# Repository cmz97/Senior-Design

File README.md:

# Senior-Design
For Detail, please refer to my personal website [here](http://chengmingzhang.com/tech-projects/projects/blog-SeniorDesign.html)

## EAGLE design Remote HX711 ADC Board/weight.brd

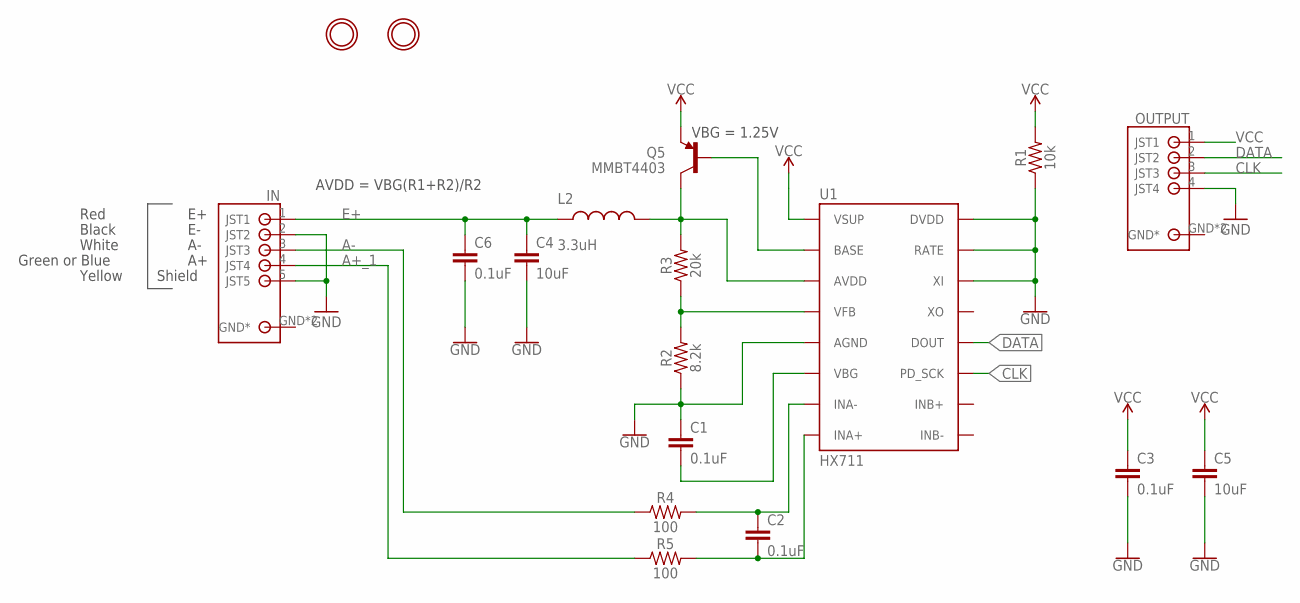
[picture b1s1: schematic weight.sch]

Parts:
C1, C2, C3, C6: 0.1uF; 0603
C4, C5: 10uF; 0603
IN: S5B-PH-SM4_TB
L2: 3.3uH; 0805
OUTPUT: S4B-PH-SM4_TB
Q5: MMBT4403; SOT23-3
R1: 10k; 0603
R2: 8.2k; 0603
R3: 20k; 0603
R4, R5: 100; 0603
U1: HX711; SO16
U$4, U$49: MOUNTINGHOLE2.5; MOUNTINGHOLE_2.5_PLATED

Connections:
A+_1: IN.4 (JST4), R5.1
A-: IN.3 (JST3), R4.1
CLK: OUTPUT.3 (JST3), U1.11 (PD_SCK)
DATA: OUTPUT.2 (JST2), U1.12 (DOUT)
E+: C4.1, C6.1, IN.1 (JST1), L2.1
GND: C1.1, C3.2, C4.2, C5.2, C6.2, IN.2 (JST2), IN.5 (JST5), OUTPUT.4 (JST4), R1.1, R2.1, U1.5 (AGND), U1.14 (XI), U1.15 (RATE), U1.16 (DVDD)
unnamed: C2.2, R5.2, U1.8 (INA+)
unnamed: Q5.1 (B), U1.2 (BASE)
unnamed: R2.2, R3.1, U1.4 (VFB)
unnamed: C1.2, U1.6 (VBG)
unnamed: L2.2, Q5.3 (C), R3.2, U1.3 (AVDD)
unnamed: C2.1, R4.2, U1.7 (INA-)
VCC: C3.1, C5.1, OUTPUT.1 (JST1), Q5.2 (E), R1.2, U1.1 (VSUP)

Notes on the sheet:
AVDD = VBG(R1+R2)/R2
Red
Black
White
Green or Blue
Shield
Yellow
VBG = 1.25V

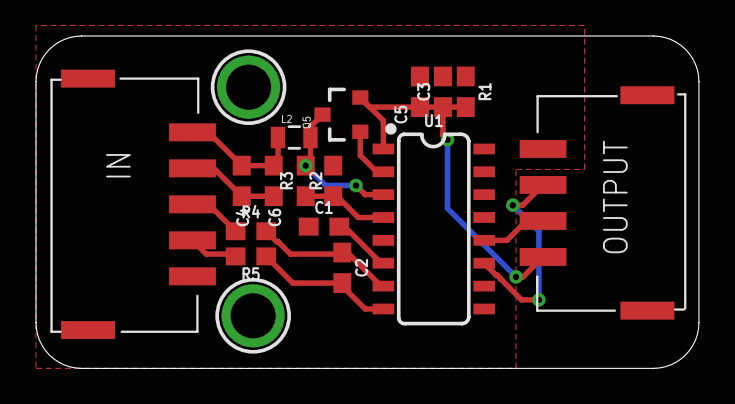
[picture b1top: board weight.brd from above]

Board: 2 copper layers, 36.8 x 18.5 mm, 18 parts (0 on the bottom side), 13 nets.

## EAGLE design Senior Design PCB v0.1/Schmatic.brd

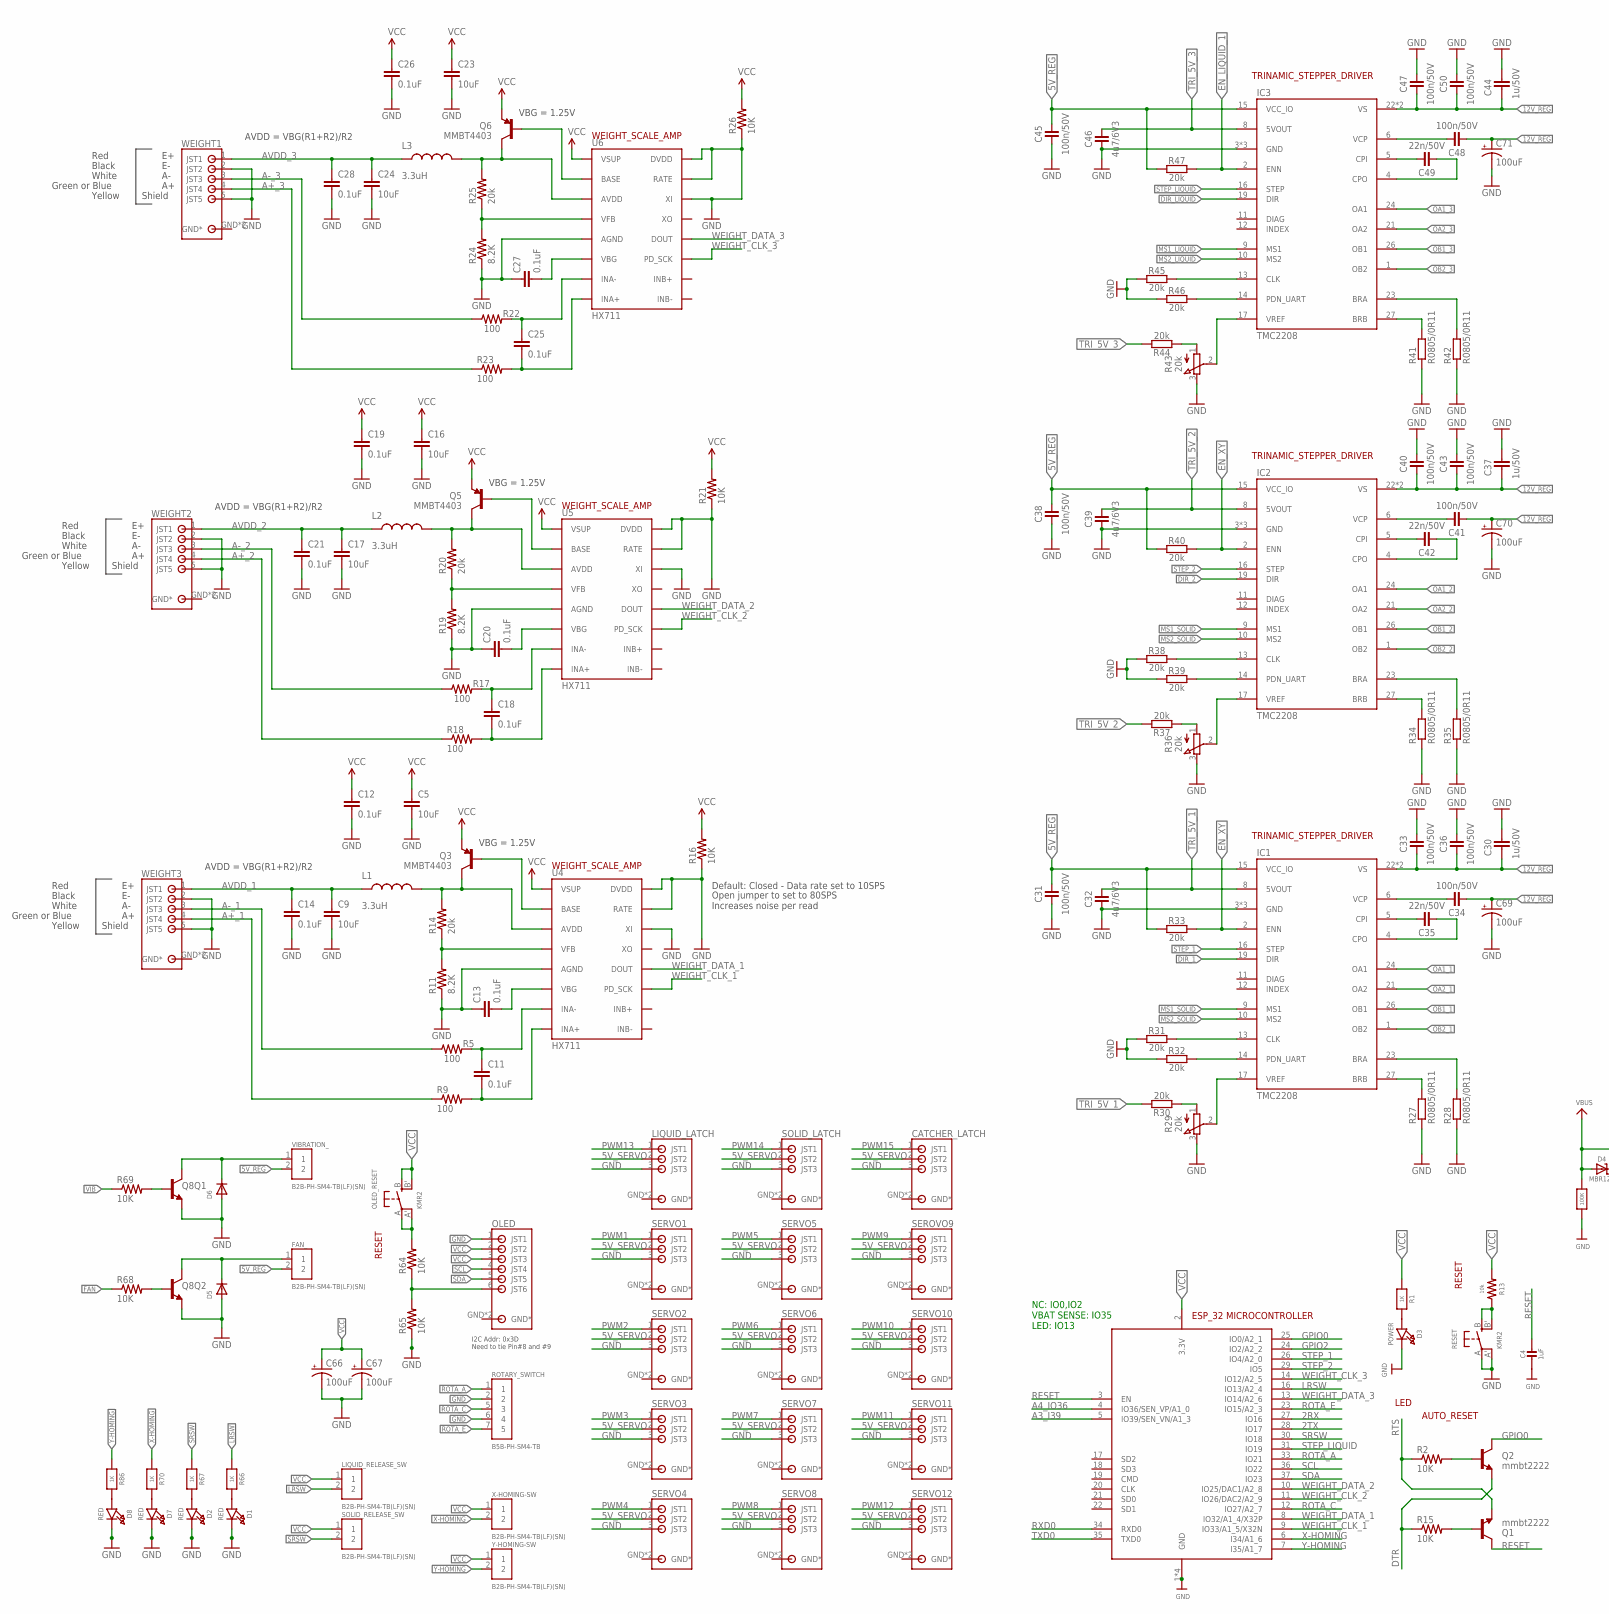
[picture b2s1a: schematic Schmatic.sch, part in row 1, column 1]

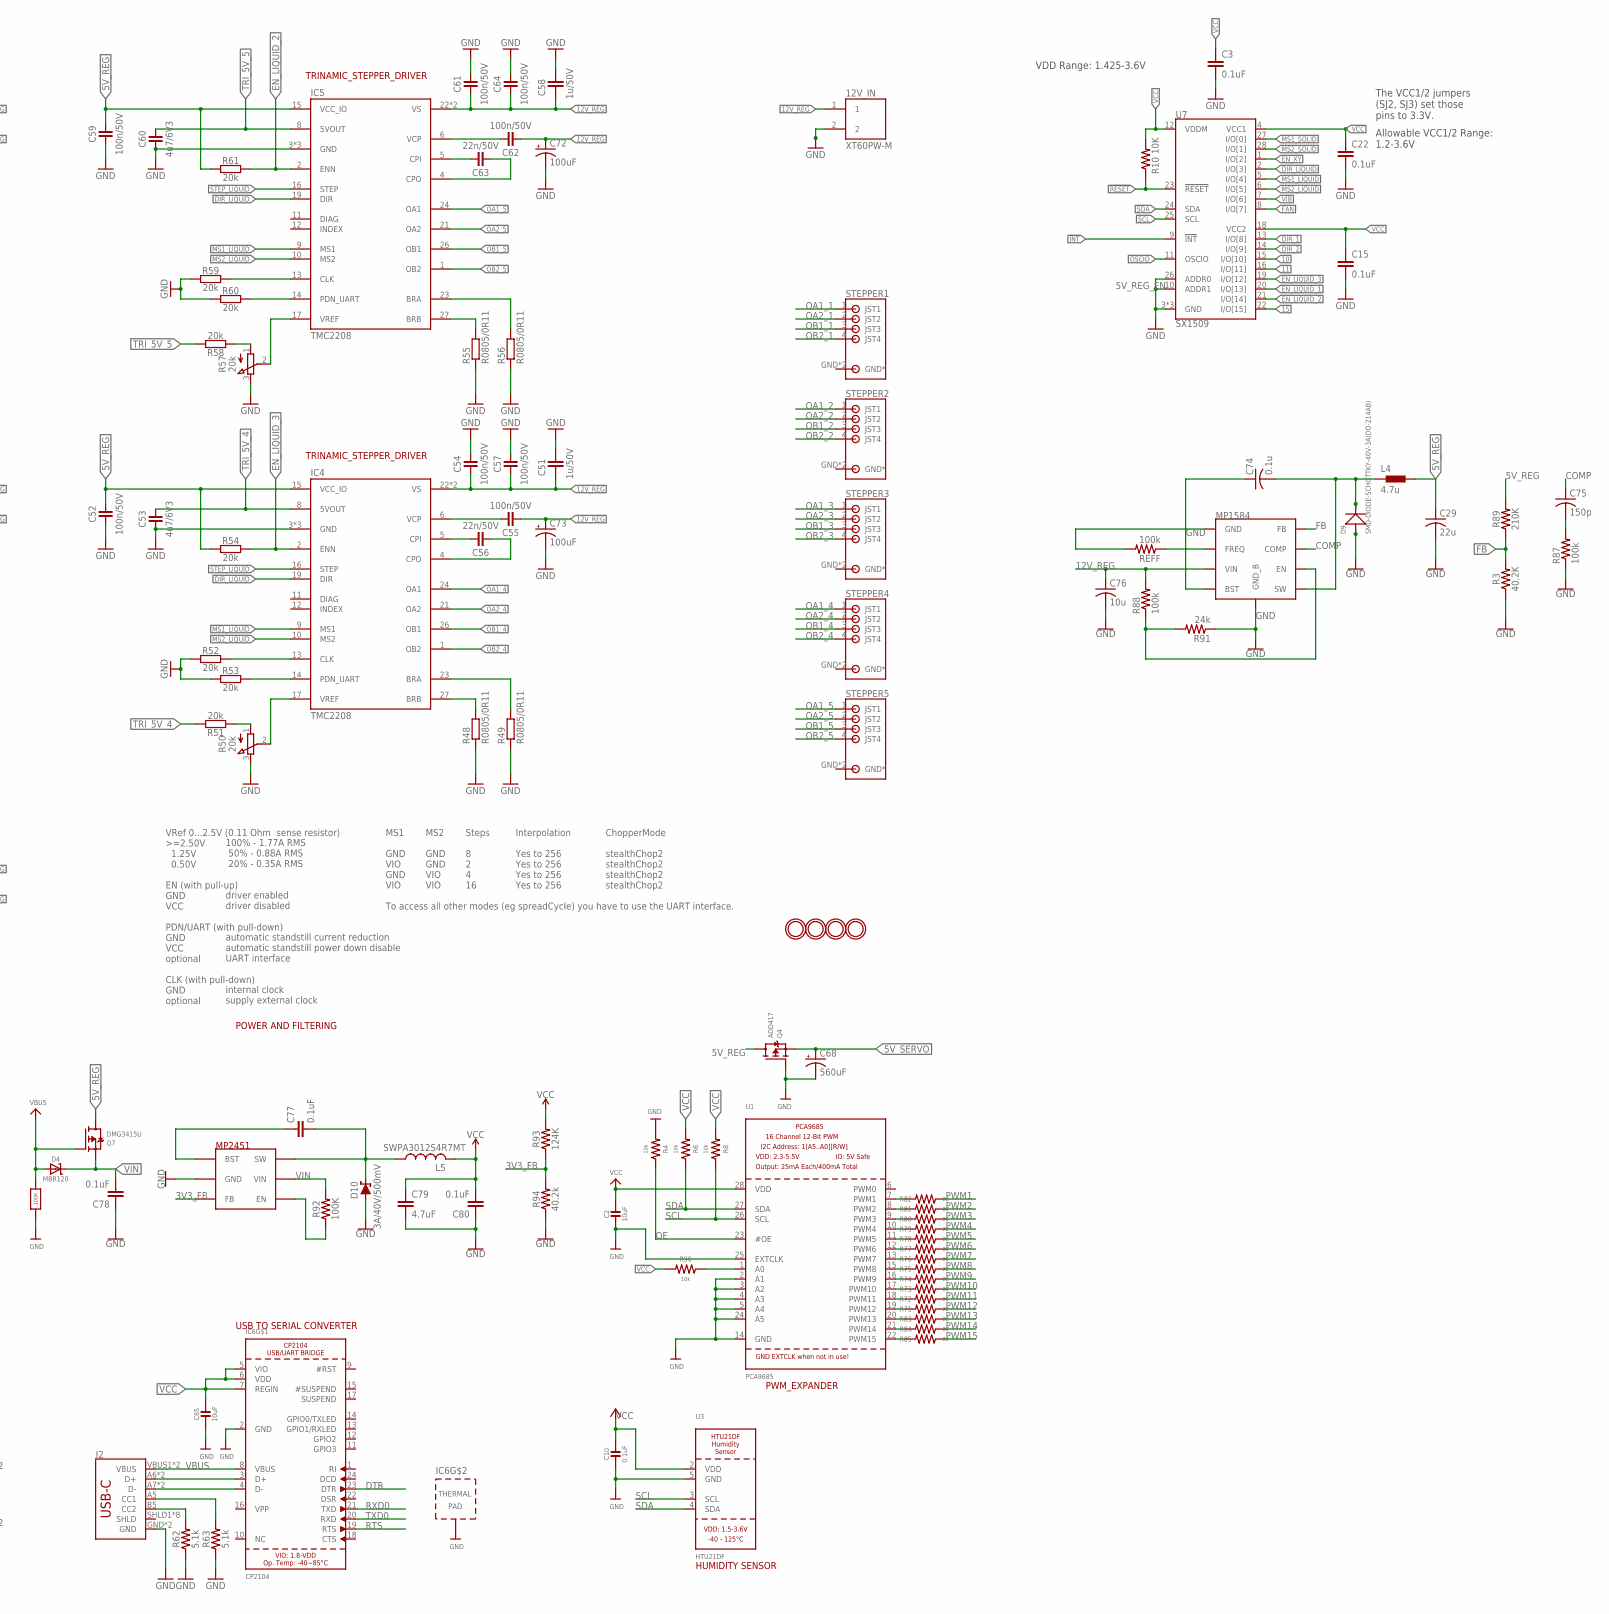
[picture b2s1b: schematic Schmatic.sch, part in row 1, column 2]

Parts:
12V_IN: XT60PW-M; AMASS_XT60PW-M
C2, C65: 10uF; 0805-NO
C3, C15, C22: 0.1uF; 0603-CAP
C4: 1uF; 0603-NO
C5, C9, C16, C17, C23, C24: 10uF; 1210
C10: 0.1uF; 0805-NO
C11, C12, C13, C14, C18, C19, C20, C21, C25, C26, C27, C28: 0.1uF; 0603-CAP@1
C29: 22u; C1206
C30, C37, C44, C51, C58: 1u/50V; C0805
C31, C33, C34, C36, C38, C40, C41, C43, C45, C47, C48, C50, C52, C54, C55, C57, C59, C61, C62, C64: 100n/50V; C0402
C32, C39, C46, C53, C60: 4u7/6V3; C0402
C35, C42, C49, C56, C63: 22n/50V; C0402
C66, C67, C69, C70, C71, C72, C73: 100uF; PANASONIC_D
C68: 560uF; PANASONIC_G
C74: 0.1u; C0603
C75: 150p; C0603
C76: 10u; C1206
C77, C78, C80: 0.1uF; 0603
C79: 4.7uF; 1206
CATCHER_LATCH: S3B-PH-SM4_TB
D1, D2, D7, D8: RED; CHIPLED_0805_NOOUTLINE
D3: POWER; CHIPLED_0805_NOOUTLINE
D4: MBR120; SOD-123
D5, D6: DIODESOD-323F; SOD-323F
D9: SMD-DIODE-SCHOTTKY-40V-3A(DO-214AB); DO-214AB
D10: 3A/40V/500mV; SMA-DIODE
FAN_: B2B-PH-SM4-TB(LF)(SN); JST_B2B-PH-SM4-TB(LF)(SN)
IC1, IC2, IC3, IC4, IC5: TMC2208; QFN28-PAD
IC6: CP2104; QFN24_4MM_SMSC
J2: USB_C16PIN; USB-C-16P
L1, L2, L3: 3.3uH; 0805
L4: 4.7u; MHCI0603-4R7M-R8
L5: SWPA3012S4R7MT; L3230M
LIQUID_LATCH: S3B-PH-SM4_TB
LIQUID_RELEASE_SW: B2B-PH-SM4-TB(LF)(SN); JST_B2B-PH-SM4-TB(LF)(SN)
MP2451: MP2451; TSOT-23-6-SOT-23-6
OLED: S6B-PH-SM4_TB
OLED_RESET: KMR2; BTN_KMR2_4.6X2.8
Q1, Q2: mmbt2222; SOT23-3
Q3, Q5, Q6: MMBT4403; SOT23-3
Q4: AOD417; TO252
Q7: DMG3415U; SOT23-R
Q8: TRANS_NPN_DUAL-MBT3904DW1T1; SC70-6
R1, R66, R67, R70, R86: 1K; 0603-NO
R2, R10, R15, R16, R21, R26, R64, R65, R68, R69: 10K; 0603-RES
R3: 40.2K; 0603
R4, R6, R8, R13, R90: 10k; 0603
R5, R9, R17, R18, R22, R23: 100; 0603-RES@1
R11, R19, R24: 8.2K; 0603-RES@1
R12: 100K; 0603-NO
R14, R20, R25: 20k; 0603-RES@1
R27, R28, R34, R35, R41, R42, R48, R49, R55, R56: R0805/0R11; M0805
R29, R36, R43, R50, R57: 20k; POT_EVM3R
R30, R31, R32, R33, R37, R38, R39, R40, R44, R45, R46, R47, R51, R52, R53, R54, R58, R59, R60, R61: 20k; C0402
R62, R63: 5.1k; 0603
R71, R72, R73, R74, R75, R76, R77, R78, R79, R80, R81, R82, R83, R84, R85: 22; 0603
R87, R88: 100k; R0603
R89: 210K; 0603
R91: 24k; R0603
R92: 100K; 0603
R93: 124K; 0603
R94: 40.2k; 0603
REFF: 100k; R0603
RESET: KMR2; BTN_KMR2_4.6X2.8
ROTARY_SWITCH: B5B-PH-SM4-TB; JST_B5B-PH-SM4-TB
SEROVO9: S3B-PH-SM4_TB
SERVO1, SERVO2, SERVO3, SERVO4, SERVO5, SERVO6, SERVO7, SERVO8, SERVO10, SERVO11, SERVO12: S3B-PH-SM4_TB
SOLID_LATCH: S3B-PH-SM4_TB
SOLID_RELEASE_SW: B2B-PH-SM4-TB(LF)(SN); JST_B2B-PH-SM4-TB(LF)(SN)
STEPPER1, STEPPER2, STEPPER3, STEPPER4, STEPPER5: S4B-PH-SM4_TB
U1: PCA9685; TSSOP28
U3: HTU21DF
U4, U5, U6: HX711; SO16
U7: SX1509; QFN-28
U$2: MP1584_V2
U$4, U$48, U$49, U$50: MOUNTINGHOLE2.5; MOUNTINGHOLE_2.5_PLATED
VIBRATION_: B2B-PH-SM4-TB(LF)(SN); JST_B2B-PH-SM4-TB(LF)(SN)
WEIGHT1, WEIGHT2, WEIGHT3: S5B-PH-SM4_TB
X2: ESP32_WROOM32_SKINNY; WROOM32_SKINNY
X-HOMING-SW: B2B-PH-SM4-TB(LF)(SN); JST_B2B-PH-SM4-TB(LF)(SN)
Y-HOMING-SW: B2B-PH-SM4-TB(LF)(SN); JST_B2B-PH-SM4-TB(LF)(SN)

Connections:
2RX: X2.27 (IO16)
2TX: X2.28 (IO17)
3V3_FB: MP2451.PIN3 (FB), R93.1, R94.2
5V_REG: C29.1, C31.2, C38.2, C45.2, C52.2, C59.2, FAN_.2, IC1.15 (VCC_IO), IC2.15 (VCC_IO), IC3.15 (VCC_IO), IC4.15 (VCC_IO), IC5.15 (VCC_IO), L4.P$2 (2), Q4.3 (D), Q7.3 (D), R33.1, R40.1, R47.1, R54.1, R61.1, R89.2, VIBRATION_.2
5V_REG_EN: R88.1, R91.2, U$2.EN
5V_SERVO: C68.+, CATCHER_LATCH.2 (JST2), LIQUID_LATCH.2 (JST2), Q4.2 (S), SEROVO9.2 (JST2), SERVO1.2 (JST2), SERVO2.2 (JST2), SERVO3.2 (JST2), SERVO4.2 (JST2), SERVO5.2 (JST2), SERVO6.2 (JST2), SERVO7.2 (JST2), SERVO8.2 (JST2), SERVO10.2 (JST2), SERVO11.2 (JST2), SERVO12.2 (JST2), SOLID_LATCH.2 (JST2)
10: U7.15 (I/O[10])
11: U7.16 (I/O[11])
12V_REG: 12V_IN.1, C30.1, C33.1, C34.1, C36.1, C37.1, C40.1, C41.1, C43.1, C44.1, C47.1, C48.1, C50.1, C51.1, C54.1, C55.1, C57.1, C58.1, C61.1, C62.1, C64.1, C69.+, C70.+, C71.+, C72.+, C73.+, C76.1, IC1.22 (VS), IC1.28 (VS), IC2.22 (VS), IC2.28 (VS), IC3.22 (VS), IC3.28 (VS), IC4.22 (VS), IC4.28 (VS), IC5.22 (VS), IC5.28 (VS), R88.2, U$2.VIN
15: U7.22 (I/O[15])
!INT: U7.9 (!INT)
!RESET: R10.1, U7.23 (!RESET)
A3_I39: X2.5 (IO39/SEN_VN/A1_3)
A4_IO36: X2.4 (IO36/SEN_VP/A1_0)
A+_1: R9.1, WEIGHT3.4 (JST4)
A+_2: R18.1, WEIGHT2.4 (JST4)
A+_3: R23.1, WEIGHT1.4 (JST4)
A-_1: R5.1, WEIGHT3.3 (JST3)
A-_2: R17.1, WEIGHT2.3 (JST3)
A-_3: R22.1, WEIGHT1.3 (JST3)
AVDD_1: C9.1, C14.1, L1.1, WEIGHT3.1 (JST1)
AVDD_2: C17.1, C21.1, L2.1, WEIGHT2.1 (JST1)
AVDD_3: C24.1, C28.1, L3.1, WEIGHT1.1 (JST1)
BRA: IC1.23 (BRA), R28.2
BRA1: IC2.23 (BRA), R35.2
BRA2: IC3.23 (BRA), R42.2
BRA3: IC4.23 (BRA), R49.2
BRA4: IC5.23 (BRA), R56.2
BRB: IC1.27 (BRB), R27.2
BRB1: IC2.27 (BRB), R34.2
BRB2: IC3.27 (BRB), R41.2
BRB3: IC4.27 (BRB), R48.2
BRB4: IC5.27 (BRB), R55.2
BST: C74.1, U$2.BST
CC1: J2.A5 (CC1), R63.2
CC2: J2.B5 (CC2), R62.2
CLK_1: IC1.13 (CLK), R31.2
CLK_2: IC2.13 (CLK), R38.2
CLK_3: IC3.13 (CLK), R45.2
CLK_4: IC4.13 (CLK), R52.2
CLK_5: IC5.13 (CLK), R59.2
COMP: C75.1, U$2.COMP
CPI: C35.2, IC1.5 (CPI)
CPI1: C42.2, IC2.5 (CPI)
CPI2: C49.2, IC3.5 (CPI)
CPI3: C56.2, IC4.5 (CPI)
CPI4: C63.2, IC5.5 (CPI)
CPO: C35.1, IC1.4 (CPO)
CPO1: C42.1, IC2.4 (CPO)
CPO2: C49.1, IC3.4 (CPO)
CPO3: C56.1, IC4.4 (CPO)
CPO4: C63.1, IC5.4 (CPO)
DIR_1: IC1.19 (DIR), U7.13 (I/O[8])
DIR_2: IC2.19 (DIR), U7.14 (I/O[9])
DIR_LIQUID: IC3.19 (DIR), IC4.19 (DIR), IC5.19 (DIR), U7.2 (I/O[3])
DTR: IC6.23 (DTR), Q2.2 (E), R15.1
EN_LIQUID_1: IC3.2 (ENN), R47.2, U7.20 (I/O[13])
EN_LIQUID_2: IC5.2 (ENN), R61.2, U7.21 (I/O[14])
EN_LIQUID_3: IC4.2 (ENN), R54.2, U7.19 (I/O[12])
EN_XY: IC1.2 (ENN), IC2.2 (ENN), R33.2, R40.2, U7.1 (I/O[2])
FAN: R68.1, U7.8 (I/O[7])
FAN_5V: D5.C, FAN_.1, Q8.6 (C)
FB: R3.2, R89.1, U$2.FB
FREQ: REFF.1, U$2.FREQ
GND: 12V_IN.2, C2.2, C3.2, C4.2, C5.2, C9.2, C10.2, C12.2, C13.1, C14.2, C15.2, C16.2, C17.2, C19.2, C20.1, C21.2, C22.2, C23.2, C24.2, C26.2, C27.1, C28.2, C29.2, C30.2, C31.1, C32.1, C33.2, C36.2, C37.2, C38.1, C39.1, C40.2, C43.2, C44.2, C45.1, C46.1, C47.2, C50.2, C51.2, C52.1, C53.1, C54.2, C57.2, C58.2, C59.1, C60.1, C61.2, C64.2, C65.2, C66.-, C67.-, C68.-, C69.-, C70.-, C71.-, C72.-, C73.-, C76.2, C78.1, C79.2, C80.1, CATCHER_LATCH.3 (JST3), D1.C, D2.C, D3.C, D5.A, D6.A, D7.C, D8.C, D9.1 (+), D10.A, IC1.3 (GND), IC1.18 (GND), IC1.TP (GND), IC2.3 (GND), IC2.18 (GND), IC2.TP (GND), IC3.3 (GND), IC3.18 (GND), IC3.TP (GND), IC4.3 (GND), IC4.18 (GND), IC4.TP (GND), IC5.3 (GND), IC5.18 (GND), IC5.TP (GND), IC6.2 (GND), IC6.THERM (TP), J2.GND, J2.GND2 (GND), LIQUID_LATCH.3 (JST3), MP2451.PIN2 (GND), OLED.1 (JST1), Q4.1 (G), Q8.1 (E), Q8.4 (E), R3.1, R4.2, R11.1, R12.1, R16.1, R19.1, R21.1, R24.1, R26.1, R27.1, R28.1, R29.3 (E), R31.1, R32.1, R34.1, R35.1, R36.3 (E), R38.1, R39.1, R41.1, R42.1, R43.3 (E), R45.1, R46.1, R48.1, R49.1, R50.3 (E), R52.1, R53.1, R55.1, R56.1, R57.3 (E), R59.1, R60.1, R62.1, R63.1, R65.1, R87.1, R91.1, R94.1, REFF.2, RESET.A, RESET.A' (P1), ROTARY_SWITCH.2, ROTARY_SWITCH.6 (4), SEROVO9.3 (JST3), SERVO1.3 (JST3), SERVO2.3 (JST3), SERVO3.3 (JST3), SERVO4.3 (JST3), SERVO5.3 (JST3), SERVO6.3 (JST3), SERVO7.3 (JST3), SERVO8.3 (JST3), SERVO10.3 (JST3), SERVO11.3 (JST3), SERVO12.3 (JST3), SOLID_LATCH.3 (JST3), U1.2 (A1), U1.3 (A2), U1.4 (A3), U1.5 (A4), U1.14 (GND), U1.24 (A5), U1.25 (EXTCLK), U3.5 (GND), U4.5 (AGND), U4.14 (XI), U4.15 (RATE), U4.16 (DVDD), U5.5 (AGND), U5.14 (XI), U5.15 (RATE), U5.16 (DVDD), U6.5 (AGND), U6.14 (XI), U6.15 (RATE), U6.16 (DVDD), U7.3 (GND), U7.10 (ADDR1), U7.17 (GND), U7.26 (ADDR0), U7.29 (GND), U$2.GND, U$2.GND_B, WEIGHT1.2 (JST2), WEIGHT1.5 (JST5), WEIGHT2.2 (JST2), WEIGHT2.5 (JST5), WEIGHT3.2 (JST2), WEIGHT3.5 (JST5), X2.1 (GND), X2.15 (GND), X2.38 (GND), X2.P$1 (GND)
GPIO0: Q2.3 (C), X2.25 (IO0/A2_1)
GPIO2: X2.24 (IO2/A2_2)
LRSW: LIQUID_RELEASE_SW.2, R66.1, X2.16 (IO13/A2_4)
MS1_LIQUID: IC3.9 (MS1), IC4.9 (MS1), IC5.9 (MS1), U7.5 (I/O[4])
MS1_SOLID: IC1.9 (MS1), IC2.9 (MS1), U7.27 (I/O[0])
MS2_LIQUID: IC3.10 (MS2), IC4.10 (MS2), IC5.10 (MS2), U7.6 (I/O[5])
MS2_SOLID: IC1.10 (MS2), IC2.10 (MS2), U7.28 (I/O[1])
unnamed: C13.2, U4.6 (VBG)
unnamed: L1.2, Q3.3 (C), R14.2, U4.3 (AVDD)
unnamed: Q5.1 (B), U5.2 (BASE)
unnamed: Q3.1 (B), U4.2 (BASE)
unnamed: D3.A, R1.2
unnamed: R11.2, R14.1, U4.4 (VFB)
unnamed: C11.1, R5.2, U4.7 (INA-)
unnamed: C11.2, R9.2, U4.8 (INA+)
unnamed: C75.2, R87.2
unnamed: R19.2, R20.1, U5.4 (VFB)
unnamed: Q1.1 (B), R15.2
unnamed: Q2.1 (B), R2.2
unnamed: C20.2, U5.6 (VBG)
unnamed: L2.2, Q5.3 (C), R20.2, U5.3 (AVDD)
unnamed: C18.1, R17.2, U5.7 (INA-)
unnamed: C18.2, R18.2, U5.8 (INA+)
unnamed: OLED_RESET.A, OLED_RESET.A' (P1), R64.2
unnamed: Q6.1 (B), U6.2 (BASE)
unnamed: R24.2, R25.1, U6.4 (VFB)
unnamed: C27.2, U6.6 (VBG)
unnamed: L3.2, Q6.3 (C), R25.2, U6.3 (AVDD)
unnamed: C25.1, R22.2, U6.7 (INA-)
unnamed: C25.2, R23.2, U6.8 (INA+)
unnamed: MP2451.PIN4 (EN), R92.1
unnamed: IC6.3 (D+), J2.A6 (D+), J2.B6 (D+)
unnamed: IC6.4 (D-), J2.A7 (D-), J2.B7 (D-)
unnamed: C77.1, MP2451.PIN1 (BST)
unnamed: R90.1, U1.1 (A0)
unnamed: C77.2, D10.C, L5.1, MP2451.PIN6 (SW)
unnamed: D1.A, R66.2
unnamed: OLED.6 (JST6), R64.1, R65.2
unnamed: Q8.5 (B), R69.2
unnamed: D2.A, R67.2
unnamed: Q8.2 (B), R68.2
unnamed: R71.2, U1.19 (PWM12)
unnamed: R72.2, U1.18 (PWM11)
unnamed: R73.2, U1.17 (PWM10)
unnamed: R74.2, U1.16 (PWM9)
unnamed: R75.2, U1.15 (PWM8)
unnamed: R76.2, U1.13 (PWM7)
unnamed: R77.2, U1.12 (PWM6)
unnamed: R78.2, U1.11 (PWM5)
unnamed: R79.2, U1.10 (PWM4)
unnamed: R80.2, U1.9 (PWM3)
unnamed: R81.2, U1.8 (PWM2)
unnamed: R82.2, U1.7 (PWM1)
unnamed: R83.2, U1.20 (PWM13)
unnamed: R84.2, U1.21 (PWM14)
unnamed: R85.2, U1.22 (PWM15)
unnamed: D7.A, R70.2
unnamed: R13.1, RESET.B (S), RESET.B' (S1)
unnamed: D8.A, R86.2
OA1_1: IC1.24 (OA1), STEPPER1.1 (JST1)
OA1_2: IC2.24 (OA1), STEPPER2.1 (JST1)
OA1_3: IC3.24 (OA1), STEPPER3.1 (JST1)
OA1_4: IC4.24 (OA1), STEPPER4.1 (JST1)
OA1_5: IC5.24 (OA1), STEPPER5.1 (JST1)
OA2_1: IC1.21 (OA2), STEPPER1.2 (JST2)
OA2_2: IC2.21 (OA2), STEPPER2.2 (JST2)
OA2_3: IC3.21 (OA2), STEPPER3.2 (JST2)
OA2_4: IC4.21 (OA2), STEPPER4.2 (JST2)
OA2_5: IC5.21 (OA2), STEPPER5.2 (JST2)
OB1_1: IC1.26 (OB1), STEPPER1.3 (JST3)
OB1_2: IC2.26 (OB1), STEPPER2.3 (JST3)
OB1_3: IC3.26 (OB1), STEPPER3.3 (JST3)
OB1_4: IC4.26 (OB1), STEPPER4.3 (JST3)
OB1_5: IC5.26 (OB1), STEPPER5.3 (JST3)
OB2_1: IC1.1 (OB2), STEPPER1.4 (JST4)
OB2_2: IC2.1 (OB2), STEPPER2.4 (JST4)
OB2_3: IC3.1 (OB2), STEPPER3.4 (JST4)
OB2_4: IC4.1 (OB2), STEPPER4.4 (JST4)
OB2_5: IC5.1 (OB2), STEPPER5.4 (JST4)
OE: R4.1, U1.23 (#OE)
OSCIO: U7.11 (OSCIO)
PDN_UART_1: IC1.14 (PDN_UART), R32.2
PDN_UART_2: IC2.14 (PDN_UART), R39.2
PDN_UART_3: IC3.14 (PDN_UART), R46.2
PDN_UART_4: IC4.14 (PDN_UART), R53.2
PDN_UART_5: IC5.14 (PDN_UART), R60.2
PWM1: R82.1, SERVO1.1 (JST1)
PWM2: R81.1, SERVO2.1 (JST1)
PWM3: R80.1, SERVO3.1 (JST1)
PWM4: R79.1, SERVO4.1 (JST1)
PWM5: R78.1, SERVO5.1 (JST1)
PWM6: R77.1, SERVO6.1 (JST1)
PWM7: R76.1, SERVO7.1 (JST1)
PWM8: R75.1, SERVO8.1 (JST1)
PWM9: R74.1, SEROVO9.1 (JST1)
PWM10: R73.1, SERVO10.1 (JST1)
PWM11: R72.1, SERVO11.1 (JST1)
PWM12: R71.1, SERVO12.1 (JST1)
PWM13: LIQUID_LATCH.1 (JST1), R83.1
PWM14: R84.1, SOLID_LATCH.1 (JST1)
PWM15: CATCHER_LATCH.1 (JST1), R85.1
RESET: C4.1, Q1.3 (C), X2.3 (EN)
ROTA_A: ROTARY_SWITCH.1, X2.33 (IO21)
ROTA_C: ROTARY_SWITCH.5 (3), X2.12 (IO27/A2_7)
ROTA_E: ROTARY_SWITCH.7 (5), X2.23 (IO15/A2_3)
RTS: IC6.19 (RTS), Q1.2 (E), R2.1
RXD0: IC6.21 (TXD), X2.34 (RXD0)
SCL: OLED.4 (JST4), R8.1, U1.26 (SCL), U3.3 (SCL), U7.25 (SCL), X2.36 (IO22)
SDA: OLED.5 (JST5), R6.1, U1.27 (SDA), U3.4 (SDA), U7.24 (SDA), X2.37 (IO23)
SRSW: R67.1, SOLID_RELEASE_SW.2, X2.30 (IO18)
STEP_1: IC1.16 (STEP), X2.26 (IO4/A2_0)
STEP_2: IC2.16 (STEP), X2.29 (IO5)
STEP_LIQUID: IC3.16 (STEP), IC4.16 (STEP), IC5.16 (STEP), X2.31 (IO19)
SW: C74.2, D9.2 (-), L4.P$1 (1), U$2.SW
TRI_5V_1: C32.2, IC1.8 (5VOUT), R30.2
TRI_5V_2: C39.2, IC2.8 (5VOUT), R37.2
TRI_5V_3: C46.2, IC3.8 (5VOUT), R44.2
TRI_5V_4: C53.2, IC4.8 (5VOUT), R51.2
TRI_5V_5: C60.2, IC5.8 (5VOUT), R58.2
TXD0: IC6.20 (RXD), X2.35 (TXD0)
VBUS: D4.A, IC6.8 (VBUS), J2.VBUS1 (VBUS), J2.VBUS2 (VBUS), Q7.1 (G), R12.2
VCC: C2.1, C3.1, C5.1, C10.1, C12.1, C15.1, C16.1, C19.1, C22.1, C23.1, C26.1, C65.1, C66.+, C67.+, C79.1, C80.2, IC6.5 (VIO), IC6.6 (VDD), IC6.7 (REGIN), L5.2, LIQUID_RELEASE_SW.1, OLED.2 (JST2), OLED.3 (JST3), OLED_RESET.B (S), OLED_RESET.B' (S1), Q3.2 (E), Q5.2 (E), Q6.2 (E), R1.1, R6.2, R8.2, R10.2, R13.2, R16.2, R21.2, R26.2, R90.2, R93.2, SOLID_RELEASE_SW.1, U1.28 (VDD), U3.2 (VDD), U4.1 (VSUP), U5.1 (VSUP), U6.1 (VSUP), U7.4 (VCC1), U7.12 (VDDM), U7.18 (VCC2), X2.2 (3.3V), X-HOMING-SW.1, Y-HOMING-SW.1
VCP: C34.2, IC1.6 (VCP)
VCP1: C41.2, IC2.6 (VCP)
VCP2: C48.2, IC3.6 (VCP)
VCP3: C55.2, IC4.6 (VCP)
VCP4: C62.2, IC5.6 (VCP)
VIB: R69.1, U7.7 (I/O[6])
VIB_5V: D6.C, Q8.3 (C), VIBRATION_.1
VIN: C78.2, D4.C, MP2451.PIN5 (VIN), Q7.2 (S), R92.2
VREF: IC1.17 (VREF), R29.2 (S)
VREF1: R29.1 (A), R30.1
VREF2: IC2.17 (VREF), R36.2 (S)
VREF3: R36.1 (A), R37.1
VREF4: IC3.17 (VREF), R43.2 (S)
VREF5: R43.1 (A), R44.1
VREF6: IC4.17 (VREF), R50.2 (S)
VREF7: R50.1 (A), R51.1
VREF8: IC5.17 (VREF), R57.2 (S)
VREF9: R57.1 (A), R58.1
WEIGHT_CLK_1: U4.11 (PD_SCK), X2.9 (IO33/A1_5/X32N)
WEIGHT_CLK_2: U5.11 (PD_SCK), X2.11 (IO26/DAC2/A2_9)
WEIGHT_CLK_3: U6.11 (PD_SCK), X2.14 (IO12/A2_5)
WEIGHT_DATA_1: U4.12 (DOUT), X2.8 (IO32/A1_4/X32P)
WEIGHT_DATA_2: U5.12 (DOUT), X2.10 (IO25/DAC1/A2_8)
WEIGHT_DATA_3: U6.12 (DOUT), X2.13 (IO14/A2_6)
X-HOMING: R70.1, X2.6 (I34/A1_6), X-HOMING-SW.2
Y-HOMING: R86.1, X2.7 (I35/A1_7), Y-HOMING-SW.2

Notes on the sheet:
NC: IO0,IO2 VBAT SENSE: IO35 LED: IO13
POWER AND FILTERING
RESET
VBG = 1.25V
AVDD = VBG(R1+R2)/R2
Default: Closed - Data rate set to 10SPS
Open jumper to set to 80SPS Increases noise per read
Red
Black
White
Green or Blue
Shield
Yellow
VRef 0...2.5V (0.11 Ohm sense resistor) >=2.50V 1.25V 0.50V EN (with pull-up) GND VCC PDN/UART (with pull-down) GND VCC optional CLK (with pull-down) GND optional
100% - 1.77A RMS 50% - 0.88A RMS 20% - 0.35A RMS driver enabled driver disabled automatic standstill current reduction automatic standstill power down disable UART interface internal clock supply external clock
MS1 GND VIO GND VIO To access all other modes (eg spreadCycle) you have to use the UART interface.
MS2 GND GND VIO VIO
Steps 8 2 4 16
Interpolation Yes to 256 Yes to 256 Yes to 256 Yes to 256
ChopperMode stealthChop2 stealthChop2 stealthChop2 stealthChop2
USB TO SERIAL CONVERTER
I2C Addr: 0x3D Need to tie Pin#8 and #9
PWM_EXPANDER
HUMIDITY SENSOR
TRINAMIC_STEPPER_DRIVER
WEIGHT_SCALE_AMP
ESP_32 MICROCONTROLLER
AUTO_RESET
The VCC1/2 jumpers (SJ2, SJ3) set those pins to 3.3V.
VDD Range: 1.425-3.6V
Allowable VCC1/2 Range: 1.2-3.6V
LED

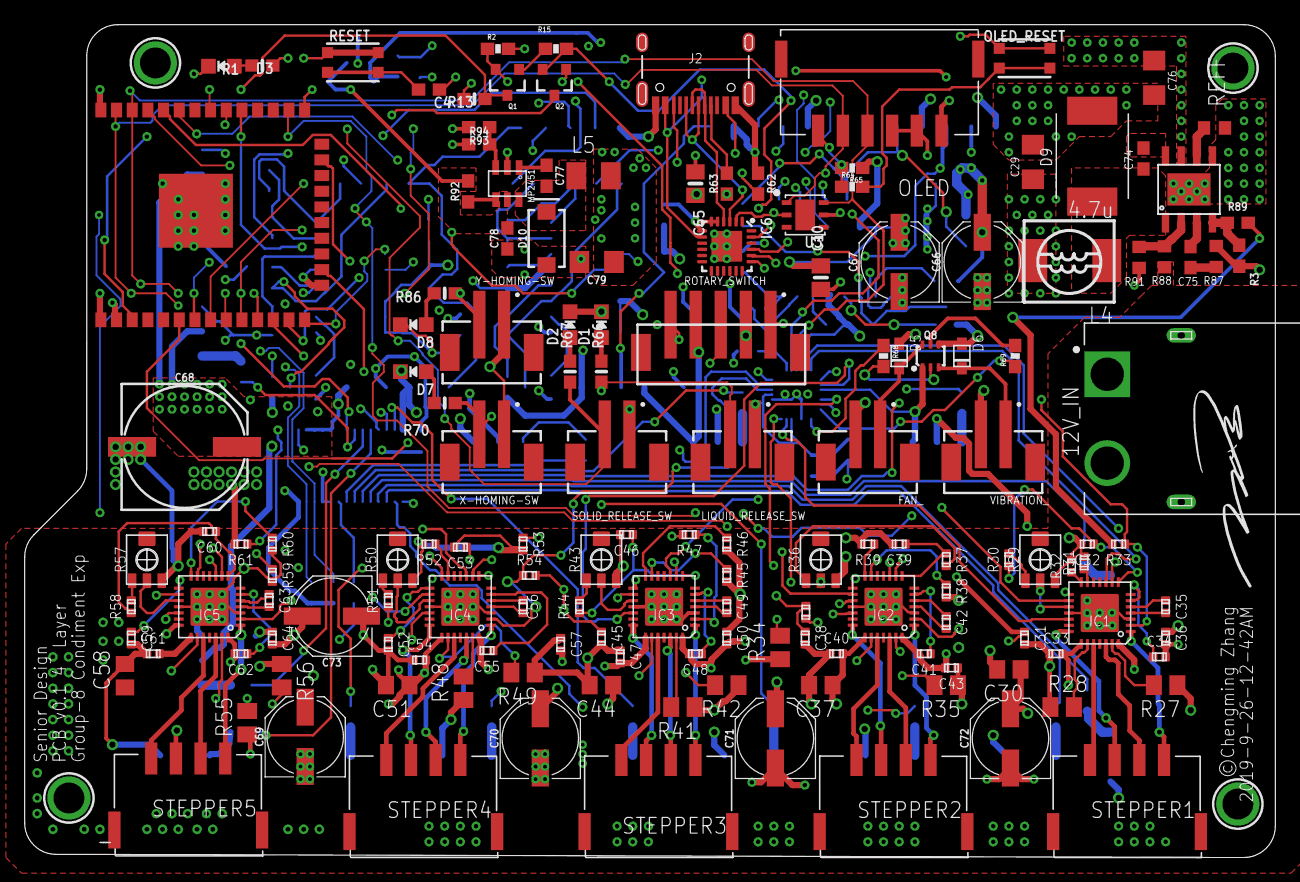
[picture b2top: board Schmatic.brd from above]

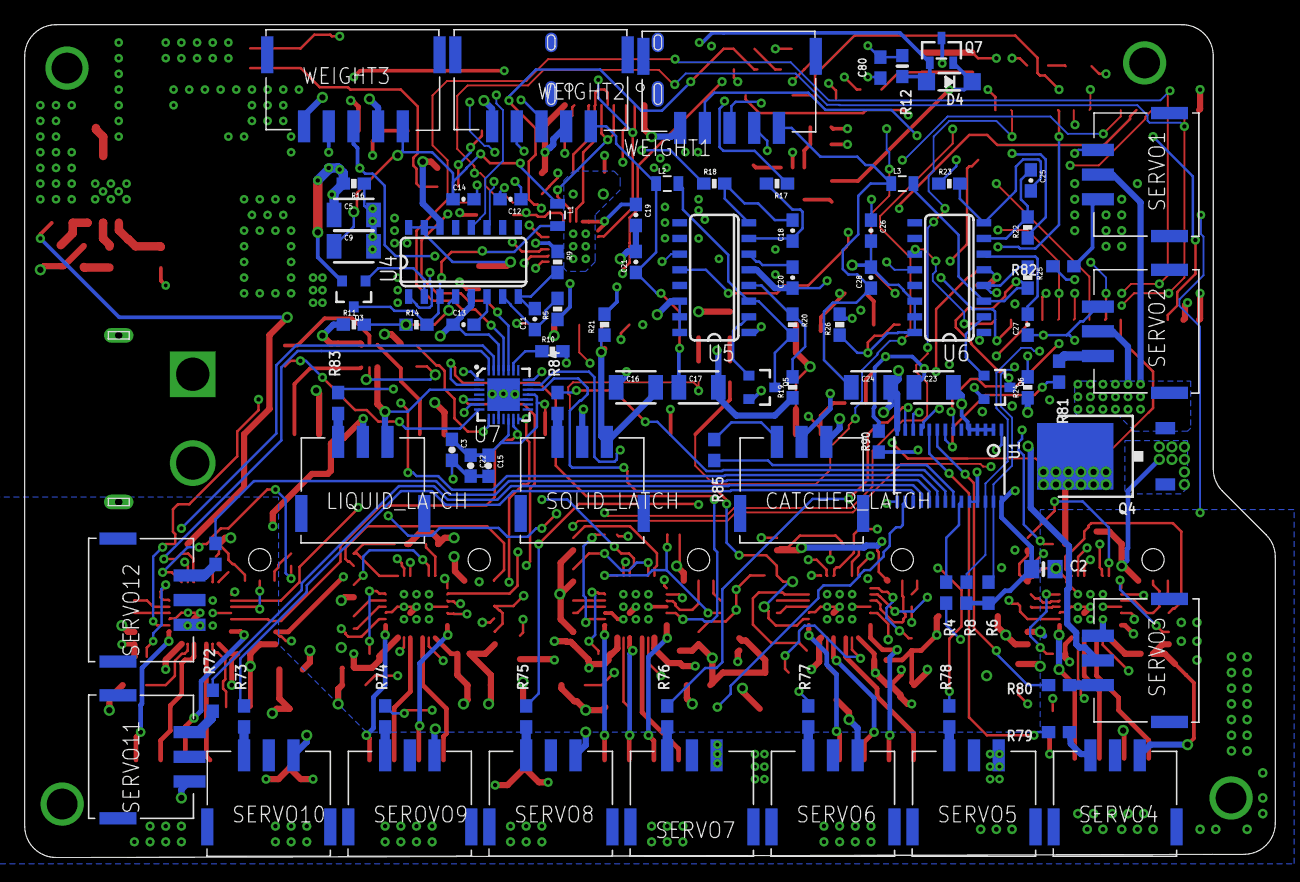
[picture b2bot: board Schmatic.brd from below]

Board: 4 copper layers, 101.3 x 67.5 mm, 247 parts (91 on the bottom side), 203 nets.

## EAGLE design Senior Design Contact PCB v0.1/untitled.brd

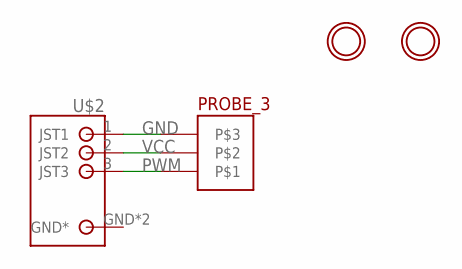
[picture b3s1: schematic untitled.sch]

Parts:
U$1: CONTACT_PROBE_3; PROBE_CONTACT
U$2: S3B-PH-SM4_TB
U$4, U$49: MOUNTINGHOLE2.5; MOUNTINGHOLE_2.5_PLATED

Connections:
GND: U$1.P$3, U$2.1 (JST1)
PWM: U$1.P$1, U$2.3 (JST3)
VCC: U$1.P$2, U$2.2 (JST2)

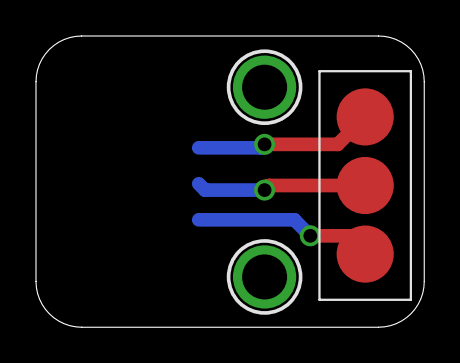
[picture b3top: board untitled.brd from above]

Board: 2 copper layers, 21.6 x 16.2 mm, 4 parts (1 on the bottom side), 3 nets.

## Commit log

2019-09-26 done all routing
2019-09-30 update on i2c expander, fixed current pour
2019-10-07 added contact board
2019-10-11 v0.3
2019-10-11 added buck 12to5 3A
2019-10-11 added vias for ground planes on buck
2019-10-11 fixed some issue with silkscreen
2019-10-13 added another buck converter for 5v to 3v3
2019-10-16 final commit to this branch
2019-10-16 removed all other junk temp board file
2019-10-16 final update
2019-10-16 board submited to factory
2019-10-18 added HX711 remote adc board, fixed main board hx7111 remote connector to 4 pin, revision board needed

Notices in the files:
Senior Design Contact PCB v0.1/untitled.brd:
©Chengming Zhang
parts and their libraries:
SparkFun-Capacitors: Licensing: Creative Commons ShareAlike 4.0 International - https://creativecommons.org/licenses/by-sa/4.0
microbuilder: This work is placed in the public domain, and may be freely used for commercial and non-commercial work with the following conditions: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
